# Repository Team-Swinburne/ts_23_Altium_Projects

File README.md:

# About

A Github repository by Team Swinburne for pcb development of the TS_22 vehicle and experimental projects. This will only contain files of the actual pcb design, more information such as design choice, circuit theory, simulation, etc can be located in the shared Pne Drive

# Getting Started

### Prerequisites
- [Altium](https://www.altium.com/solutions/academic-programs/student-licenses) (required): Used to design all of these pcb, fill in the link for a free student license.
- [Git](https://git-scm.com/) (required) : Backbone of Github.
- [Github Destop](https://desktop.github.com/) (recommended) : An UI overlay of git built specifically for Github so you don't have to deal with the terminal interface.

### Installation
Once all prerequisite are install, clone this repository to your desired folder by opening it in Github Desktop

# Usage
Follow this guide to ensure you meet the standard and is set up probably before diving into create your own pcb

### Naming
**Always** name your project strictly following the naming scheme to avoid confusion in the future. When starting a new board, create a new folder name `ts_22-"Board name"`. Then inside that folder, create a project in Altium called `YYMMDD "Board name" "Revsion number"`
#### For example:
> ts_22-Brake-Module
>
Then:
> 210705 Brake Module R0
> 
`YYMMDD` is the project's createtion date and `Revision number` starts with 0. 
#### Note: Once the pcb is made, **DO NOT** make any changes to that revision, modifying **MUST** be made by starting a new revision, e.g. R1

### Importing libraries
Altium libraries are collections of component intented for speeding up the design and manufacturing process. There are 2 libraries used in PnE: *ts_22-standard-lib* and *ts_22-connectors-lib*, located in the *~ts_22 Library*.

To import them: In Altium with your project opened, right-click on the project name -> Add Existing -> Choose file `"library name".DbLib`, do this for both libraries.

Guide on how to add components into the library will be made available in video from. Please discuss with your section leader before attempting to modify these library.

### Importing design rules
Design rules ensure all pcb meet Team Swinburne standards and more importantly, the competition rule. There are 2 sets of rules: *ts_22-rules.RUL* and *ts_22-HV-rules.RUL*. Choose the corresponding rule dependent on which board you are working on.

To import: In Altium with your project opened, choose Design -> Rules. Then in the pop-up windows, right-click on Design Rules -> Import Rules -> Select all entries -> OK -> Choose file `"rules name".RUL`.

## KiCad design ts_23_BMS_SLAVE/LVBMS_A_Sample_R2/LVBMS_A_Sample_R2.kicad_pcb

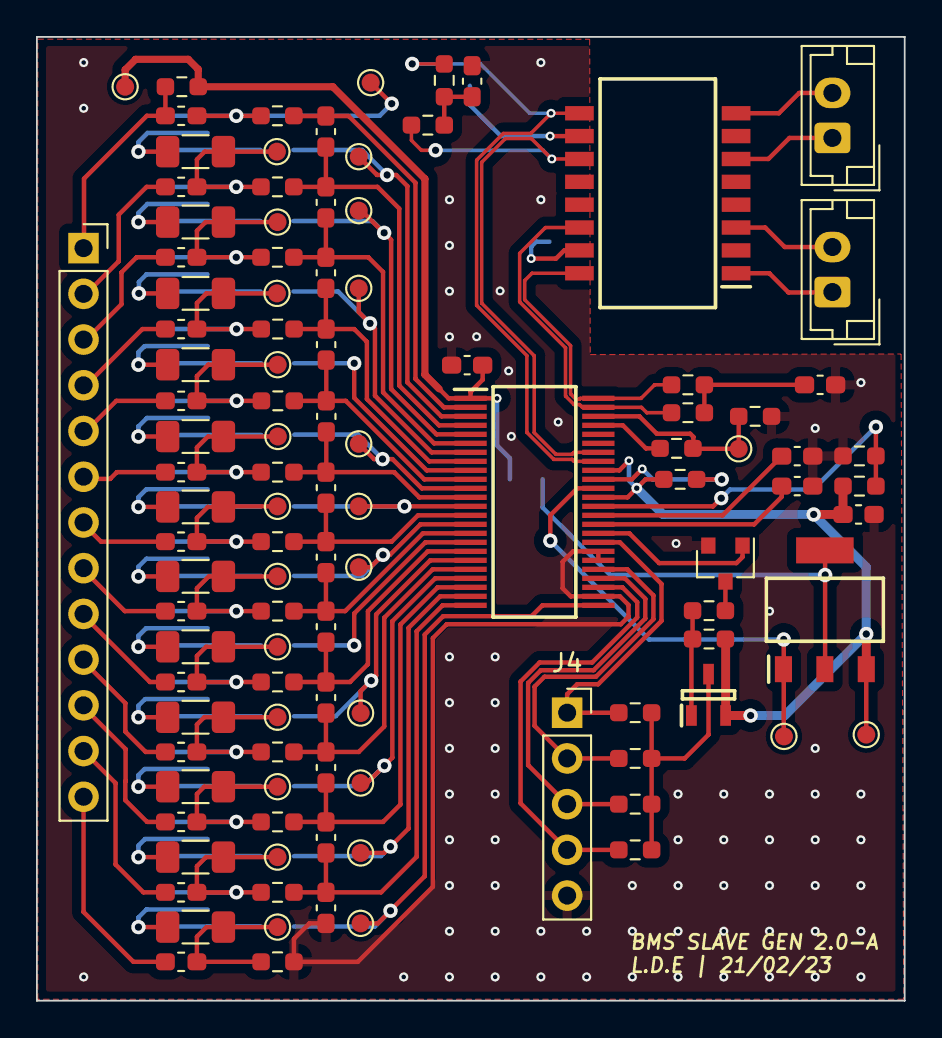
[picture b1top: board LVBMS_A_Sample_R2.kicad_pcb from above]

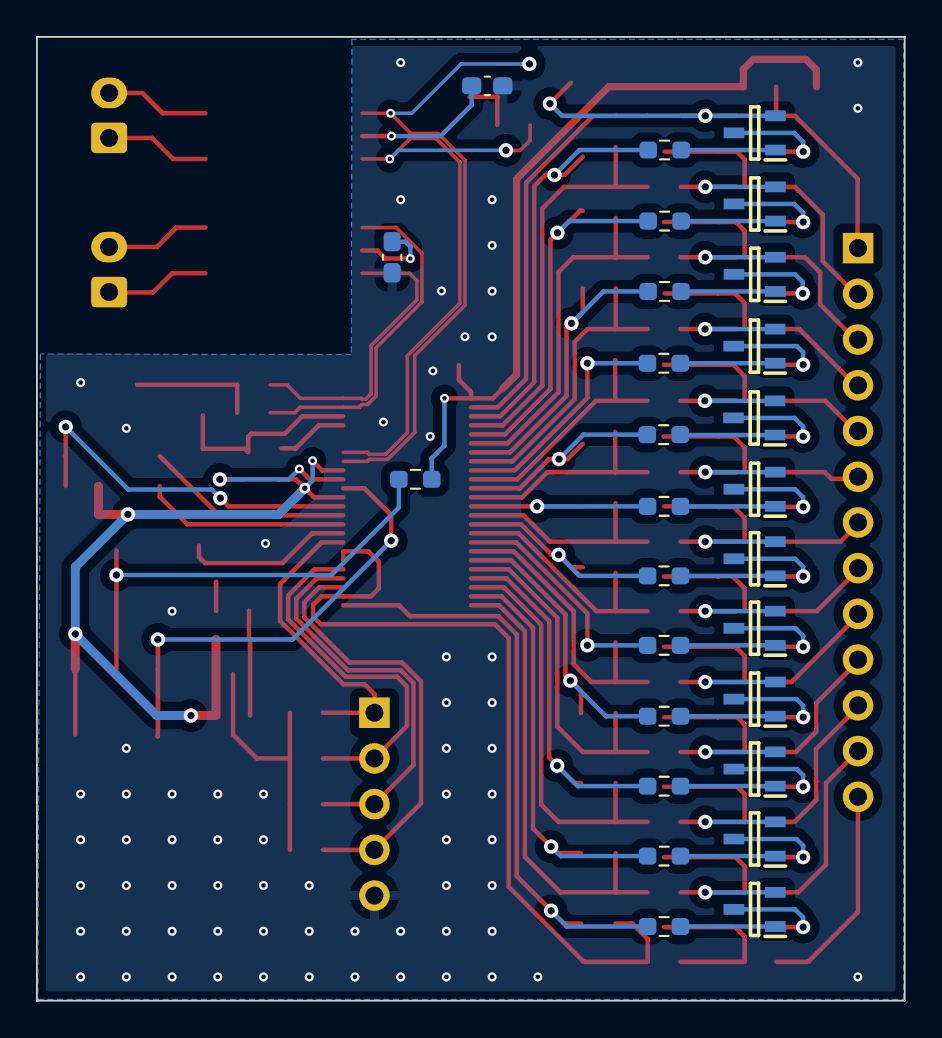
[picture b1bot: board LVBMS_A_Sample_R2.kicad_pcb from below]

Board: 2 copper layers, 48.2 x 53.5 mm, 135 parts (27 on the bottom side), 105 nets.

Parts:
C1, C18: 0.01uF; C_0603_1608Metric_Pad1.08x0.95mm_HandSolder
C2, C3, C4, C5, C6, C7, C8, C9, C10, C11, C12, C13, C14, C15, C16, C17, C19, C20: 0.1uF; C_0603_1608Metric_Pad1.08x0.95mm_HandSolder
F1, F2, F3, F4, F5, F6, F7, F8, F9, F10, F11, F12, F13: MFU0805FF04000P100; Fuse_0603_1608Metric_Pad1.05x0.95mm_HandSolder
J1, J3: S2B-PH-K-S_LF__SN_; JST_EH_B2B-EH-A_1x02_P2.50mm_Vertical
J2: Conn_01x13_Male; PinSocket_1x13_P2.54mm_Vertical
J4: Conn_01x05_Male; PinSocket_1x05_P2.54mm_Vertical
Q1, Q3, Q4, Q5, Q6, Q7, Q8, Q9, Q10, Q11, Q12, Q13, Q14: BSS308PE_H6327; SOT95P260X110-3N
Q2: CZT5551CT-ND; SOT230P700X180-4N
Q15: DTC114E; SOT-23
R1, R3, R4, R5: 50R; R_0603_1608Metric_Pad0.98x0.95mm_HandSolder
R2, R50, R51, R54: 100k; R_0603_1608Metric_Pad0.98x0.95mm_HandSolder
R6: BIAS RESISTOR (VALUE CHANGES); R_0603_1608Metric_Pad0.98x0.95mm_HandSolder
R7: 1.0M; R_0603_1608Metric_Pad0.98x0.95mm_HandSolder
R8: BIAS RESISTOR (VALUE CAN CHANGE); R_0603_1608Metric_Pad0.98x0.95mm_HandSolder
R9, R10, R11, R13, R15, R17, R19, R21, R29, R30, R31, R32, R33, R34, R35, R48, R49, R53: 100R; R_0603_1608Metric_Pad0.98x0.95mm_HandSolder
R12, R14, R16, R18, R20, R22, R23, R24, R25, R26, R27, R28: 3.3k; R_0603_1608Metric_Pad0.98x0.95mm_HandSolder
R36, R37, R38, R39, R40, R41, R42, R43, R44, R45, R46, R47: 33R; R_1206_3216Metric_Pad1.30x1.75mm_HandSolder
R52: 50k; R_0603_1608Metric_Pad0.98x0.95mm_HandSolder
T1: HX1188NL; SOIC127P940X597-16N
TP1, TP2, TP3, TP4, TP5, TP6, TP7, TP8, TP9, TP10, TP11, TP12, TP13, TP14, TP15, TP16, TP17, TP25, TP27, TP28, TP29, TP30, TP31, TP33, TP34, TP35, TP36: TestPoint; TestPoint_Pad_D1.0mm
U1: LTC6811

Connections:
/B0: F13.1, J2.13
/B1: F12.1, J2.12
/B2: F11.1, J2.11
/B3: F10.1, J2.10
/B4: F9.1, J2.9
/B5: F8.1, J2.8
/B6: F7.1, J2.7
/B8: F5.1, J2.5
/B9: F4.1, J2.4
/B10: F3.1, J2.3
/B11: F2.1, J2.2
/Balancing and Filtering/BATT_0: F13.2, R35.2, R47.2, TP16.1
/Balancing and Filtering/BATT_1: F12.2, Q14.2, R34.2, R46.2, TP15.1
/Balancing and Filtering/BATT_2: F11.2, Q13.2, R33.2, R45.2, TP14.1
/Balancing and Filtering/BATT_3: F10.2, Q12.2, R32.2, R44.2, TP13.1
/Balancing and Filtering/BATT_4: F9.2, Q11.2, R31.2, R43.2, TP12.1
/Balancing and Filtering/BATT_5: F8.2, Q10.2, R30.2, R42.2, TP11.1
/Balancing and Filtering/BATT_6: F7.2, Q9.2, R29.2, R41.2, TP10.1
/Balancing and Filtering/BATT_7: F6.2, Q8.2, R21.2, R40.2, TP9.1
/Balancing and Filtering/BATT_8: F5.2, Q7.2, R19.2, R39.2, TP8.1
/Balancing and Filtering/BATT_9: F4.2, Q6.2, R17.2, R38.2, TP7.1
/Balancing and Filtering/BATT_10: F3.2, Q5.2, R15.2, R37.2, TP6.1
/Balancing and Filtering/BATT_11: F2.2, Q4.2, R13.2, R36.2, TP5.1
/Balancing and Filtering/BATT_12: F1.2, Q3.2, R11.2, TP4.1
/C1: C16.1, C17.2, R34.1, U1.24 (C1)
/C2: C15.1, C16.2, R33.1, U1.22 (C2)
/C3: C14.1, C15.2, R32.1, U1.20 (C3)
/C4: C13.1, C14.2, R31.1, U1.18 (C4)
/C5: C12.1, C13.2, R30.1, U1.16 (C5)
/C6: C11.1, C12.2, R29.1, U1.14 (C6)
/C7: C10.1, C11.2, R21.1, U1.12 (C7)
/C8: C9.1, C10.2, R19.1, U1.10 (C8)
/C9: C8.1, C9.2, R17.1, U1.8 (C9)
/C10: C7.1, C8.2, R15.1, U1.6 (C10)
/C11: C6.1, C7.2, R13.1, U1.4 (C11)
/C12: C6.2, R11.1, U1.2 (C12)
/DTEN: R48.2, R49.2, U1.36 (DTEN)
/IMA (ISO): J3.2, T1.3 (TD-)
/IMB (ISO): J1.2, T1.8 (RD-)
/IPA (ISO): J3.1, T1.1 (TD+)
/IPB (ISO): J1.1, T1.6 (RD+)
/ISO_SPI_+: R4.1, T1.16 (TX+), U1.48 (IPB)
/ISO_SPI_-: R5.2, T1.14 (TX-), U1.47 (IMB)
/ISO_SPI_N: R3.2, T1.9 (RX-), U1.41 (CSB_(IMA))
/ISO_SPI_P: R1.1, T1.11 (RX+), U1.42 (SCK_(IPA))
/S1: R28.1, TP36.1, U1.25 (S1)
/S2: R27.1, TP35.1, U1.23 (S2)
/S3: R26.1, TP34.1, U1.21 (S3)
/S4: R25.1, TP33.1, U1.19 (S4)
/S5: R24.1, U1.17 (S5)
/S6: R23.1, TP31.1, U1.15 (S6)
/S7: R22.1, TP30.1, U1.13 (S7)
/S8: R20.1, TP29.1, U1.11 (S8)
/S9: R18.1, U1.9 (S9)
/S10: R16.1, TP28.1, U1.7 (S10)
/S11: R14.1, TP27.1, U1.5 (S11)
/S12: R12.1, TP25.1, U1.3 (S12)
/T1: J4.1, R2.1, U1.32 (GPIO4)
/T2: J4.2, R50.1, U1.29 (GPIO3)
/T3: J4.3, R51.1, U1.28 (GPIO2)
/T4: J4.4, R54.1, U1.27 (GPIO1)
/TCON: Q15.1 (B), U1.33 (GPIO5)
/V+: F1.1, J2.1, R10.2
/VREG: C2.1, Q1.2, Q2.3 (E), R7.2, R48.1, R52.1, TP3.1, U1.37 (VREG), U1.40 (ISOMD)
/VTEMP: Q1.3, R2.2, R50.2, R51.2, R54.2
GND: C1.1, C2.2, C3.2, C4.2, C5.2, C17.1, C18.1, C19.2, C20.2, J4.5, Q15.2 (E), R8.2, R35.1, R49.1, U1.26 (C0), U1.30 (V-**), U1.31 (V-)
unnamed: C1.2, T1.15 (CMT_2)
unnamed: C3.1, U1.34 (VREF2)
unnamed: C4.1, U1.35 (VREF1)
unnamed: C5.1, R9.2, R10.1, TP2.1, U1.1 (V+)
unnamed: C18.2, T1.10 (CMT_1)
unnamed: C19.1, R1.2, R3.1
unnamed: C20.1, R4.2, R5.1
unnamed: F6.1, J2.6
unnamed: Q1.1, R52.2, R53.1
unnamed: Q2.1 (B), TP1.1, U1.38 (DRIVE)
unnamed: Q2.2 (C_1), Q2.4 (C_2), R9.1
unnamed: Q3.1, R12.2
unnamed: Q3.3, R36.1
unnamed: Q4.1, R14.2
unnamed: Q4.3, R37.1
unnamed: Q5.1, R16.2
unnamed: Q5.3, R38.1
unnamed: Q6.1, R18.2
unnamed: Q6.3, R39.1
unnamed: Q7.1, R20.2
unnamed: Q7.3, R40.1
unnamed: Q8.1, R22.2
unnamed: Q8.3, R41.1
unnamed: Q9.1, R23.2
unnamed: Q9.3, R42.1
unnamed: Q10.1, R24.2
unnamed: Q10.3, R43.1
unnamed: Q11.1, R25.2
unnamed: Q11.3, R44.1
unnamed: Q12.1, R26.2
unnamed: Q12.3, R45.1
unnamed: Q13.1, R27.2
unnamed: Q13.3, R46.1
unnamed: Q14.1, R28.2
unnamed: Q14.3, R47.1
unnamed: Q15.3 (C), R53.2
unnamed: R6.1, U1.45 (IBIAS)
unnamed: R6.2, R8.1, TP17.1, U1.46 (ICMP)
unnamed: R7.1, U1.39 (WDT)

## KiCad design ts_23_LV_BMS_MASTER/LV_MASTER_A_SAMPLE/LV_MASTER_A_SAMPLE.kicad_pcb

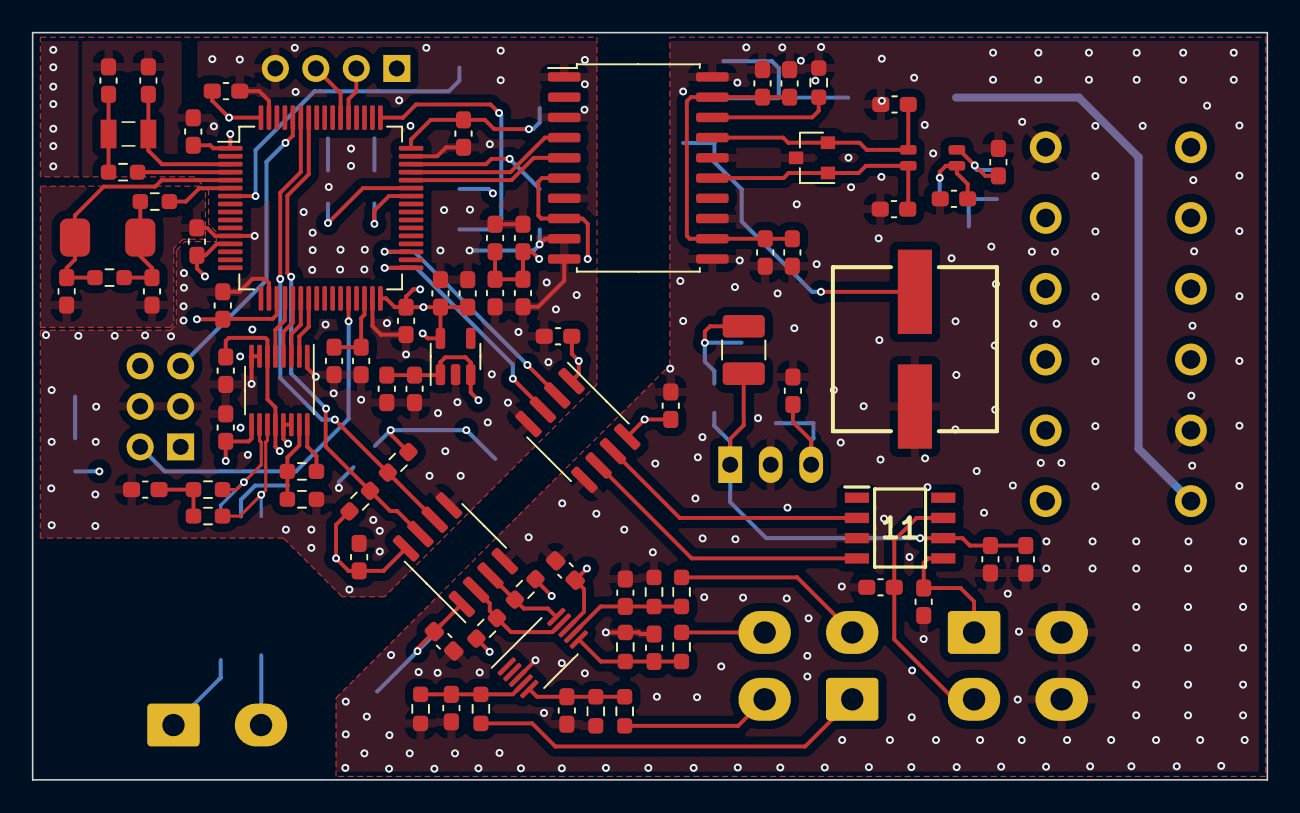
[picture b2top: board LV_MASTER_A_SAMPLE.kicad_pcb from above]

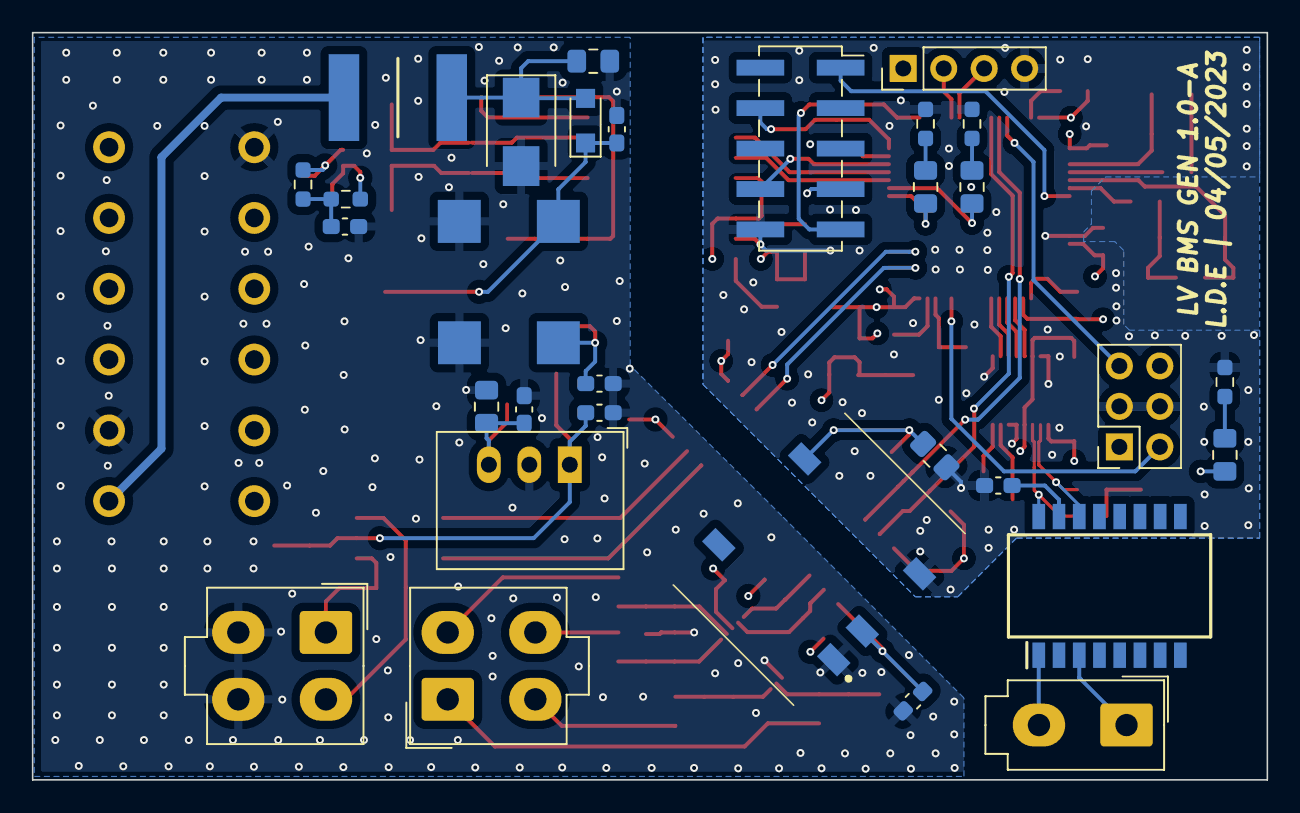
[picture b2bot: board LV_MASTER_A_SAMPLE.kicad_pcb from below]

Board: 4 copper layers, 77.5 x 46.9 mm, 111 parts (32 on the bottom side), 69 nets.

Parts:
11: IXDN604SIA; SOIC127P600X175-8N
C1, C2, C3, C4: 22pF; C_0603_1608Metric_Pad1.08x0.95mm_HandSolder
C5, C6, C7, C8, C9, C10, C22: 10.0uF; C_0603_1608Metric_Pad1.08x0.95mm_HandSolder
C11, C12: 2.2uF; C_0603_1608Metric_Pad1.08x0.95mm_HandSolder
C13, C14, C18, C21, C23, C50: 100.0nF; C_0603_1608Metric_Pad1.08x0.95mm_HandSolder
C15, C19, C49: 1.0uF; C_0603_1608Metric_Pad1.08x0.95mm_HandSolder
C16: 100.0nF; C_0805_2012Metric_Pad1.18x1.45mm_HandSolder
C17, C24: 22.0uF; C_0805_2012Metric_Pad1.18x1.45mm_HandSolder
C20: 220uF (POL); TLV_10X10.5_
C25, C27, C29, C32, C39, C40, C41, C42, C43, C44, C45, C46, C47, C48, C51, C52, C53: 0.1uF; C_0603_1608Metric_Pad1.08x0.95mm_HandSolder
C26, C30, C38: 0.01uF; C_0603_1608Metric_Pad1.08x0.95mm_HandSolder
C28, C31, C54: 10uF; C_0603_1608Metric_Pad1.08x0.95mm_HandSolder
C33, C34, C35, C36: 100pf; C_0603_1608Metric_Pad1.08x0.95mm_HandSolder
C37: 22pf; C_0603_1608Metric_Pad1.08x0.95mm_HandSolder
C55, C56: 10.0nF; C_0603_1608Metric_Pad1.08x0.95mm_HandSolder
D1, D2, D3: RED LED; C_0805_2012Metric_Pad1.18x1.45mm_HandSolder
D4: SM6T36CAY; D_SMB
D5: PMEG10010ELR; Nexperia_CFP3_SOD-123W
D6: NUP2105L; SOT-23
F1: 0ZCF0100AF2A; FUSC7451X170N
J1: DT 12P; DT12-PCB PIN
J2: UART; PinHeader_1x04_P2.54mm_Vertical
J3: BOOT1; PinSocket_2x03_P2.54mm_Vertical
J4: STLINK; PinSocket_2x05_P2.54mm_Vertical_SMD
J5: Conn_01x02_Male; Molex_Mini-Fit_Jr_5566-02A_2x01_P4.20mm_Vertical
J6, J7: Conn_02x02_Counter_Clockwise; Molex_Mini-Fit_Jr_5566-04A_2x02_P4.20mm_Vertical
L1: 744272121; WE-SL575
L2: 12uH; L_1210_3225Metric_Pad1.42x2.65mm_HandSolder
PS1: R2S-0505_HP; R2S0505HP
R1, R2, R3: 680R; R_0603_1608Metric_Pad0.98x0.95mm_HandSolder
R4: 200K; R_0603_1608Metric_Pad0.98x0.95mm_HandSolder
R5: 0R; R_0603_1608Metric_Pad0.98x0.95mm_HandSolder
R6, R7: 56R; R_0603_1608Metric_Pad0.98x0.95mm_HandSolder
R8, R9: 50R; R_0603_1608Metric_Pad0.98x0.95mm_HandSolder
R10, R11: ERJP06F1000V; R_0603_1608Metric_Pad0.98x0.95mm_HandSolder
R12, R13, R14, R15: 3.3k; R_0603_1608Metric_Pad0.98x0.95mm_HandSolder
R16, R17, R18, R19, R20, R21, R22, R23: 100k; R_0603_1608Metric_Pad0.98x0.95mm_HandSolder
R28, R29: 50mR; R_0603_1608Metric_Pad0.98x0.95mm_HandSolder
T1: HX1188NL; SOIC127P940X597-16N
U1: STM32F446RET7; LQFP-64_10x10mm_P0.5mm
U2: TLV70033_SOT23-5; SOT-23-5
U3: R-78C5.0-1.0; Converter_DCDC_RECOM_R-78E-0.5_THT
U4: ADM3053; SOIC-20W_7.5x12.8mm_P1.27mm
U5: B82786C0104H002
U6: LTC6820; MSOP-16_3x4.039mm_P0.5mm
U7: ISO1540; SOIC-8_3.9x4.9mm_P1.27mm
U8: ADS1115; VSSOP-10_3x3mm_P0.5mm
U9: ADuM120N; SOIC-8_3.9x4.9mm_P1.27mm
Y1: ECS-80-18-30-JGN-TR
Y2: FC-135_32.7680KA-A5; FC135327680KAA5

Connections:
0V_(ISO): C1.2, C2.2, C3.2, C4.2, C5.2, C6.2, C7.2, C8.2, C9.2, C10.2, C11.2, C12.2, C14.2, C15.2, C17.2, C18.2, C19.2, C25.2, C26.2, C27.2, C28.2, C38.1, C39.2, C40.2, C41.2, C42.1, C51.1, J2.4, J3.3, J3.4, J4.10, PS1.4 (-VOUT), R1.1, R2.1, R3.1, R11.2, U1.12 (VSSA), U1.18 (VSS), U1.31 (VSS), U1.47 (VSS), U1.63 (VSS), U2.2 (GND), U4.1 (GND1), U4.3 (GND1), U4.7 (GND1), U4.9 (GND1), U4.10 (GND1), U6.1 (EN), U6.7 (POL), U6.8 (PHA), U6.13 (SLOW), U6.14 (GND), U7.5 (GND2), U9.4 (GND1)
3.3V_(ISO): C5.1, C6.1, C7.1, C8.1, C9.1, C10.1, C18.1, C19.1, D1.2 (A), J2.1, J3.1, J3.6, J4.4, J4.7, U1.1 (VBAT), U1.13 (VDDA), U1.19 (VDD), U1.32 (VDD), U1.48 (VDD), U1.64 (VDD), U2.5 (OUT)
5V_(ISO): C14.1, C15.1, C17.1, C25.1, C26.1, C27.1, C28.1, C40.1, C41.1, C42.2, PS1.5 (+VOUT), R12.2, R13.2, U2.1 (IN), U2.3 (EN), U4.6 (VIO), U4.8 (VCC), U6.6 (VDDS), U6.9 (VDD), U6.12 (MSTER), U7.8 (VCC2)
+3.3V: C51.2, U9.1 (VDD1)
+5V: C13.1, C24.1, C43.2, C44.2, C49.1, C50.1, C52.2, PS1.2 (+VIN), R14.2, R15.2, U3.3 (OUT), U7.1 (VCC1), U8.8 (VDD), U9.8 (VDD2)
+24V: 11.6 (VCC), C23.1, C53.2, C54.2, L2.2, U3.1 (IN)
/AUX_OUTPUT: 11.5 (OUTB), C55.2, J7.1
/BLUE_LOOP_RLY: 11.7 (OUTA), C56.2, J7.2
/Blue Loop/AUX_OUTPUT(ISO): U1.33 (PB12_(CAN2_RX)), U9.3 (VIB)
/Blue Loop/BLUE_LOOP_RLY(ISO): U1.35 (PB14_(SPI2_MISO)), U9.2 (VIA)
/Blue Loop/IN1: 11.2 (INA), U9.7 (VOA)
/Blue Loop/IN2: 11.4 (INB), U9.6 (VOB)
/CAN1 +: C36.1, J1.4, R6.2, U5.4 (CH1)
/CAN1 -: C35.1, J1.5, R7.1, U5.3 (CH2)
/CANBUS/CAN1_RX: U1.45 (PA12_(CAN1_TX)), U4.4 (RXD)
/CANBUS/CAN1_TX: U1.44 (PA11_(CAN1_RX)), U4.5 (TXD)
/CS1A: J6.1, R16.2
/CS1B: J6.3, R20.2
/CS2A: J6.4, R18.2
/CS2B: J6.2, R22.2
/Current Sense/Input Filter/AIN0: C45.2, R16.1, R17.2, U8.4 (AIN0)
/Current Sense/Input Filter/AIN1: C47.2, R20.1, R21.2, U8.5 (AIN1)
/Current Sense/Input Filter/AIN2: C46.2, R18.1, R19.2, U8.6 (AIN2)
/Current Sense/Input Filter/AIN3: C48.2, R22.1, R23.2, U8.7 (AIN3)
/Current Sense/SCL: R14.1, U7.3 (SCL1), U8.10 (SCL)
/Current Sense/SDA: R15.1, U7.2 (SDA1), U8.9 (SDA)
/GLV+: F1.1, J1.12
/IMA: J5.1, T1.3 (TD-)
/IPA: J5.2, T1.1 (TD+)
/Microcontroller/BOOT0: J3.5, U1.60 (BOOT0)
/Microcontroller/BOOT1: J3.2, U1.28 (PB2-BOOT1_(SPI3_MOSI))
/Microcontroller/CAN_RX_IND: D2.2 (A), U1.43 (PA10)
/Microcontroller/CAN_TX_IND: D3.2 (A), U1.42 (PA9_(I2C3_SMBA_SPI2_SCK))
/Microcontroller/CS: U1.20 (PA4_(SPI1/3_NSS)), U6.5 (CS)
/Microcontroller/MISO: U1.22 (PA6_(SPI1_MISO)), U6.3 (MISO)
/Microcontroller/MOSI: U1.23 (PA7_(SPI1_MOSI)), U6.2 (MOSI)
/Microcontroller/NRST: J4.1, U1.7 (NRST)
/Microcontroller/SCK: U1.21 (PA5_(SPI1_SCK)), U6.4 (SCK)
/Microcontroller/SCL_(ISO): R12.1, U1.58 (PB6_(I2C1_SCL)), U7.7 (SDA2)
/Microcontroller/SDA_(ISO): R13.1, U1.59 (PB7_(I2C1_SDA)), U7.6 (SCL2)
/Microcontroller/SWCLK: J4.9, U1.49 (PA14_(JTCK-SWCLK))
/Microcontroller/SWDIO: J4.8, U1.46 (PA13_(JTMS-SWDIO))
/Microcontroller/UART_RX: J2.3, U1.54 (PD2)
/Microcontroller/UART_TX: J2.2, U1.53 (PC12)
/Microcontroller/VCAP_1: C11.1, C12.1, U1.30 (VCAP_1)
/Microcontroller/XTAL32_IN: C4.1, U1.3 (PC14_(OSC32_IN)), Y2.2
/Microcontroller/XTAL32_OUT: R29.2, U1.4 (PC15_(OSC32_OUT))
/Microcontroller/XTAL_IN: C1.1, R4.2, U1.5 (PH0_(OSC_IN)), Y1.1 (XTAL_IN)
/Microcontroller/XTAL_OUT: R28.1, U1.6 (PH1_(OSC_OUT))
/isoSPI/ISO_SPI_N: R9.2, T1.14 (TX-), U6.10 (IM)
/isoSPI/ISO_SPI_P: R8.1, T1.16 (TX+), U6.11 (IP)
GND: 11.3 (GND), C13.2, C16.2, C20.2, C21.2, C22.2, C23.2, C24.2, C29.2, C30.2, C31.2, C32.2, C33.2, C34.2, C35.2, C36.2, C37.2, C43.1, C44.1, C45.1, C46.1, C47.1, C48.1, C49.2, C50.2, C52.1, C53.1, C54.1, C55.1, C56.1, D4.2 (A2), D6.3 (A), J1.1, J1.11, J7.3, J7.4, L1.3 (2), L1.4 (1), PS1.1 (-VIN), R5.1, R17.1, R19.1, R21.1, R23.1, U3.2 (GND), U4.11 (GND2), U4.13 (GND2), U4.16 (GND2), U4.20 (GND2), U7.4 (GND1), U8.3 (GND), U9.5 (GND2)
unnamed: C2.1, R4.1, R28.2, Y1.2 (XTAL_OUT)
unnamed: C3.1, R29.1, Y2.1
unnamed: C16.1, D4.1 (A1), D5.2 (A), F1.2
unnamed: C20.1, C21.1, D5.1 (K), L1.1 (3)
unnamed: C29.1, C30.1, C31.1, C32.1, U4.12 (VISOOUT), U4.19 (VISOIN)
unnamed: C33.1, D6.2 (K), U4.17 (CANH), U5.1 (CH1)
unnamed: C34.1, D6.1 (K), U4.15 (CANL), U5.2 (CH2)
unnamed: C37.1, R6.1, R7.2
unnamed: C38.2, T1.15 (CMT_2)
unnamed: C39.1, R8.2, R9.1
unnamed: D1.1 (K), R1.2
unnamed: D2.1 (K), R2.2
unnamed: D3.1 (K), R3.2
unnamed: C22.1, L1.2 (4), L2.1
unnamed: R5.2, U4.18 (RS)
unnamed: R10.1, U6.16 (IBIAS)
unnamed: R10.2, R11.1, U6.15 (ICMP)

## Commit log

2023-04-17 New boards
2023-04-17 Aero board
2023-04-20 Power supply
2023-04-21 Dashboard Breakout Board Started
    Schematic almost complete, just needs power supply added. Made for 4 buttons and a potentiometer. Uses 1 CAN line with Molex MicroFit connectors
2023-04-21 Dashboard: First components placed
2023-04-22 Dashboard Rev 1 has been completed
    Ready for internal review
2023-04-23 Added some basic stitching to the Dash PCB
2023-04-25 Dash Step file
2023-05-09 LV_BMS_A Sample Uploads
2023-05-09 Fix Diff. Pair Routing on Slave
2023-05-10 Changes to Diff. Pair Routing
2023-05-10 resolved diff. pair routing issues on master module
2023-05-10 Last Minute Changes
2023-05-10 Minor Changes
2023-05-17 Started new power system
2023-05-18 New Power Supply - Half done
    Added a new 24 to 5 V reg that is much smaller, mostly wired up, added a bunch of new capacitors that will also be added to the standard library
2023-05-19 Dashboard PCB getting there
2023-05-21 Temp Module Progress as at 21/05/2023
    Schematic design completed. PCB design in progress. Fundamental changes in schematic and PCB design coming soon to adhere to comp rules.
2023-05-30 Dash almost finished
2023-06-03 Final Changes to board
2023-06-13 Dashboard PCB R0 completed, ready for review
2023-06-15 R0 of Dashboard Breakout Board ready for final review before Sourceman
    Terminal Board is also close to being ready for final review
2023-06-18 Terminal Board R3
    Terminal Board R3 ready for review before sending to Sourceman for manufacture
2023-06-25 LV BMS Updates
2023-06-26 Updated Gerbers
2023-07-03 Fab stuff
2023-07-03 More Fab Stuff
2023-07-03 Still more fab stuff
2023-07-03 Completed Temp Module Design
2023-07-16 Added CAD for Temp Module Assembly
2023-07-16 Update to Temp Module Assembly CAD
    Changed bolt hole diameter sizes for tabs and fixed interferences.
2023-07-17 Changes for Sourceman
2023-07-17 Changes to Temp Module for Sourceman
2023-07-28 New Brake Module Upload
2023-07-28 Brake Module R6 Layout Fixes
2023-07-31 Changes to Gerbers
2023-08-01 Brake Module Gerbers
2023-08-20 New project
2023-08-20 Rough design for PDM
    Still need to add Bridge Drivers and connect some of the comms lines to the micro
2023-08-24 ASSI Upload
2023-08-27 More work on PDM
2023-08-27 Schematic done aside from main connector
2023-09-01 PDM Schematic completed
2023-09-03 copy of pcb is what ive done for the low voltage side
2023-09-03 fixing
2023-09-03 fixed it
2023-09-03 low voltage set out
2023-09-03 Roughly placed H bridge and smart switches on PDM
2023-09-04 Fixed Blade Fuse Holder in PCB
2023-09-04 PCB PDU 24
    Added more components to the PCB, and save and pushing
2023-09-04 tracers
2023-09-05 Traces for PDM - Smart Switches are getting there
2023-09-06 PDM Smart Driver Routing continued
    About half done
2023-09-07 TS schematic for ESF mostly finished
2023-09-07 TS Schematics finished for ESF
2023-09-08 PDM progress
2023-09-08 Upload Charger Schematic V2
2023-09-09 PDM more progress
2023-09-10 PDM almost ready for submission
2023-09-20 Brake Module and Charger Items
2023-09-20 Brake Module Changes
2023-09-25 Fixed up errors
    - DECAP config on ADC
    - Added caps between AVDD/DVDD and gnd
2023-09-27 Changes made to ADC to temp sensor traces.
2023-09-27 Fixed grounding after re-routing traces.
2023-09-28 Final touch ups before second design review.
2023-09-28 Temp Module changes post PCB review.
    - Added power connector labels on backside of board.
    - Changed footprint for 24 to 5V power supply.
2023-09-28 Changed silkscreen to white.
2023-10-04 Brake Module Updates for Re-Fabrication
2023-10-17 Updated manufacturing specifications.
    Thickness, finish, copper weight specs changed.
2023-11-11 BSPD Current sense
2023-11-18 General Changes
2024-05-03 Updated Regen Control System
